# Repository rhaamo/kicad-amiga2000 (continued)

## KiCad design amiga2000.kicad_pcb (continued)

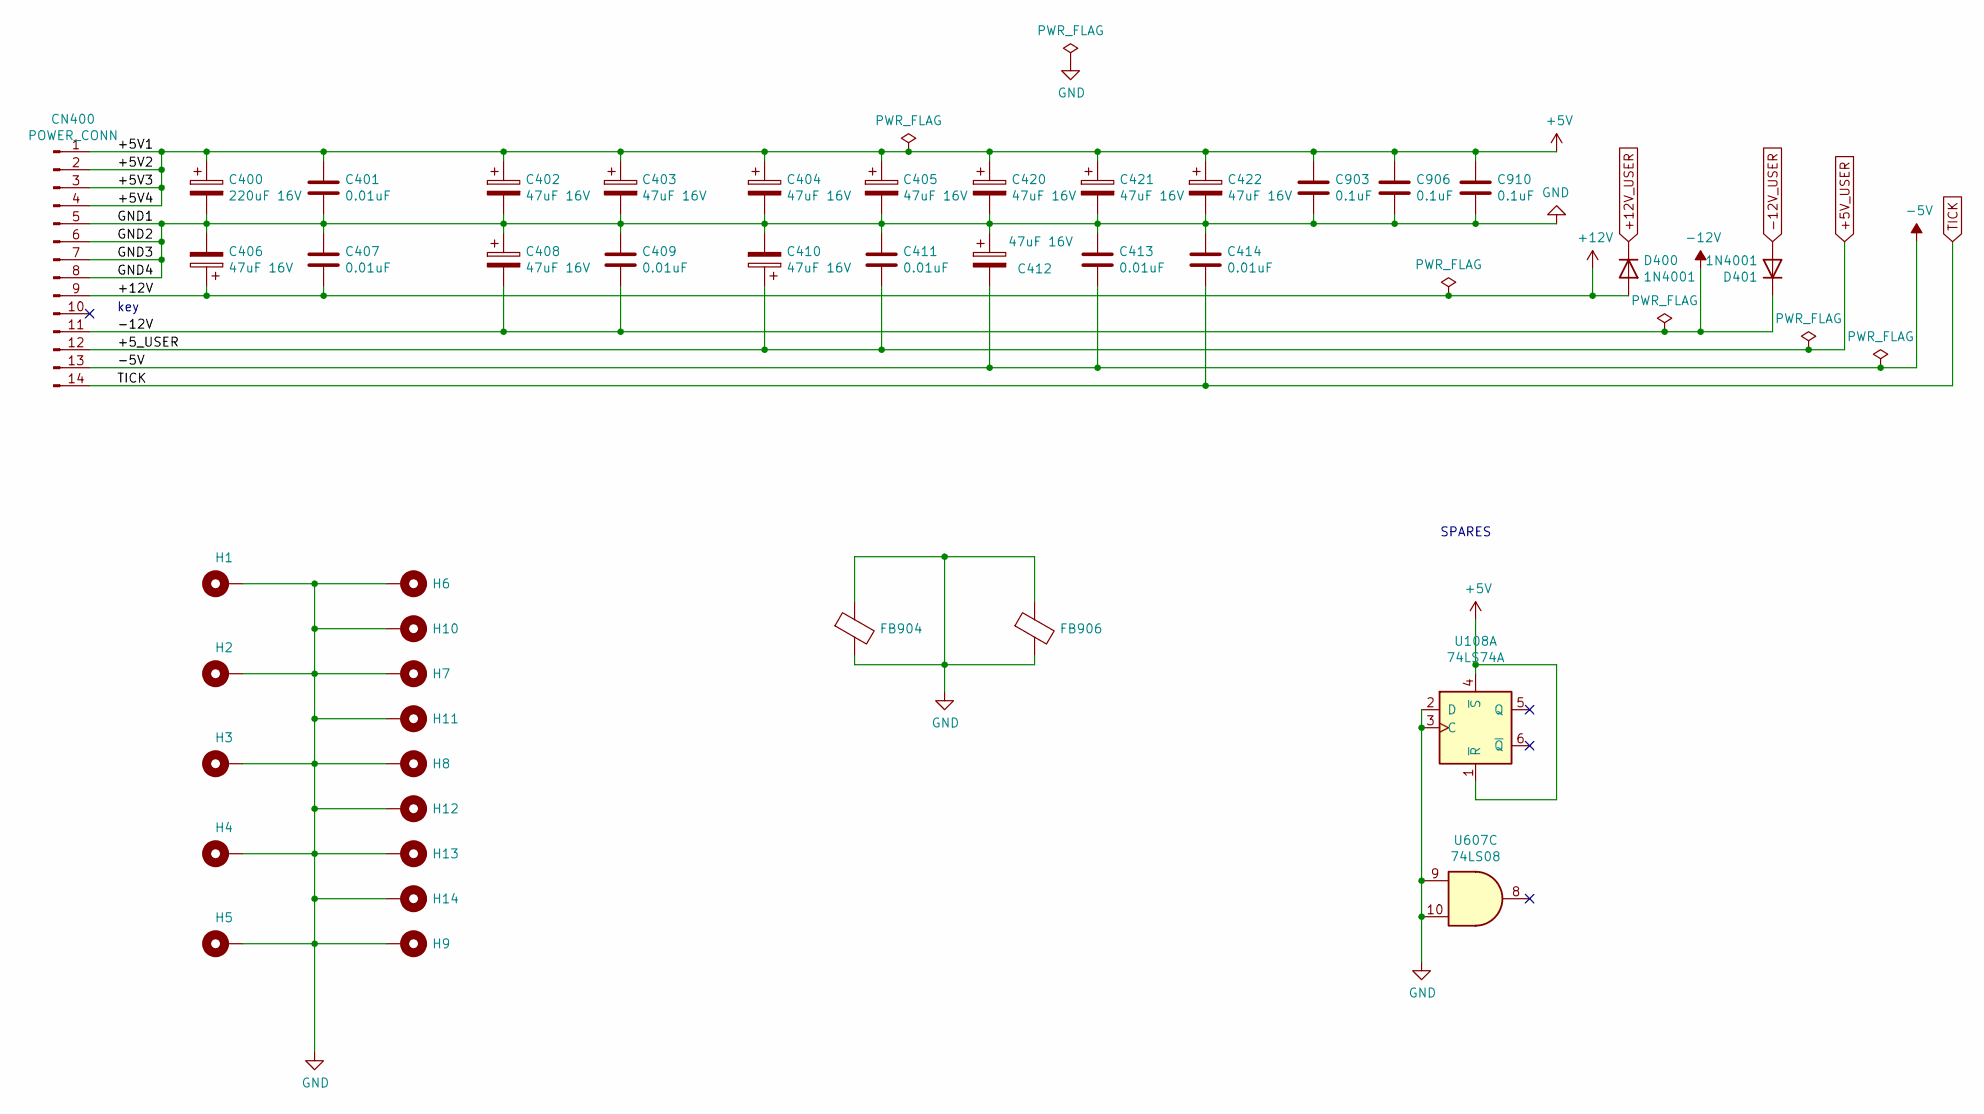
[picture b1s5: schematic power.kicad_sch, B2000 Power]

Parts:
C400: 220uF 16V; CP_Radial_Tantal_D6.0mm_P5.00mm
C401, C407, C409, C411, C413, C414: 0.01uF; C_Rect_L11.5mm_W2.6mm_P10.00mm_MKT
C402, C403, C404, C405, C406, C408, C410, C412, C420, C421, C422: 47uF 16V; CP_Radial_Tantal_D5.5mm_P5.00mm
C903, C906, C910: 0.1uF; C_Rect_L11.5mm_W2.6mm_P10.00mm_MKT
CN400: POWER_CONN; A2K_PWR
D400, D401: 1N4001; D_DO-41_SOD81_P10.16mm_Horizontal
FB904, FB906: Ferrite_Bead; L_Axial_L7.0mm_D3.3mm_P5.08mm_Vertical_Fastron_MICC
H1, H2, H3, H4, H5, H6, H7, H8, H9, H10, H11, H12, H13, H14: MountingHole_Pad; MountingHole_4mm_Pad_Via
U108: 74LS74A; DIP-14_W7.62mm_Socket
U607: 74LS08; DIP-14_W7.62mm_Socket

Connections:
+5V_USER: C410.1, C411.2, CN400.12; also elsewhere on the board
+12V: C406.1, C407.2, CN400.9, D400.2 (A); also elsewhere on the board
+12V_USER: D400.1 (K); also elsewhere on the board
-5V: C412.2, C413.2, CN400.13; also elsewhere on the board
-12V: C408.2, C409.2, CN400.11, D401.1 (K); also elsewhere on the board
-12V_USER: D401.2 (A); also elsewhere on the board
GND: C400.2, C401.2, C402.2, C403.2, C404.2, C405.2, C406.2, C407.1, C408.1, C409.1, C410.2, C411.1, C412.1, C413.1, C414.1, C420.2, C421.2, C422.2, C903.2, C906.2, C910.2, CN400.5, CN400.6, CN400.7, CN400.8, FB904.1, FB904.2, FB906.1, FB906.2, H1.1, H2.1, H3.1, H4.1, H5.1, H6.1, H7.1, H8.1, H9.1, H10.1, H11.1, H12.1, H13.1, H14.1, U108.2 (D), U108.3 (C), U607.9, U607.10; also elsewhere on the board
TICK: C414.2, CN400.14; also elsewhere on the board

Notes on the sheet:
key
SPARES

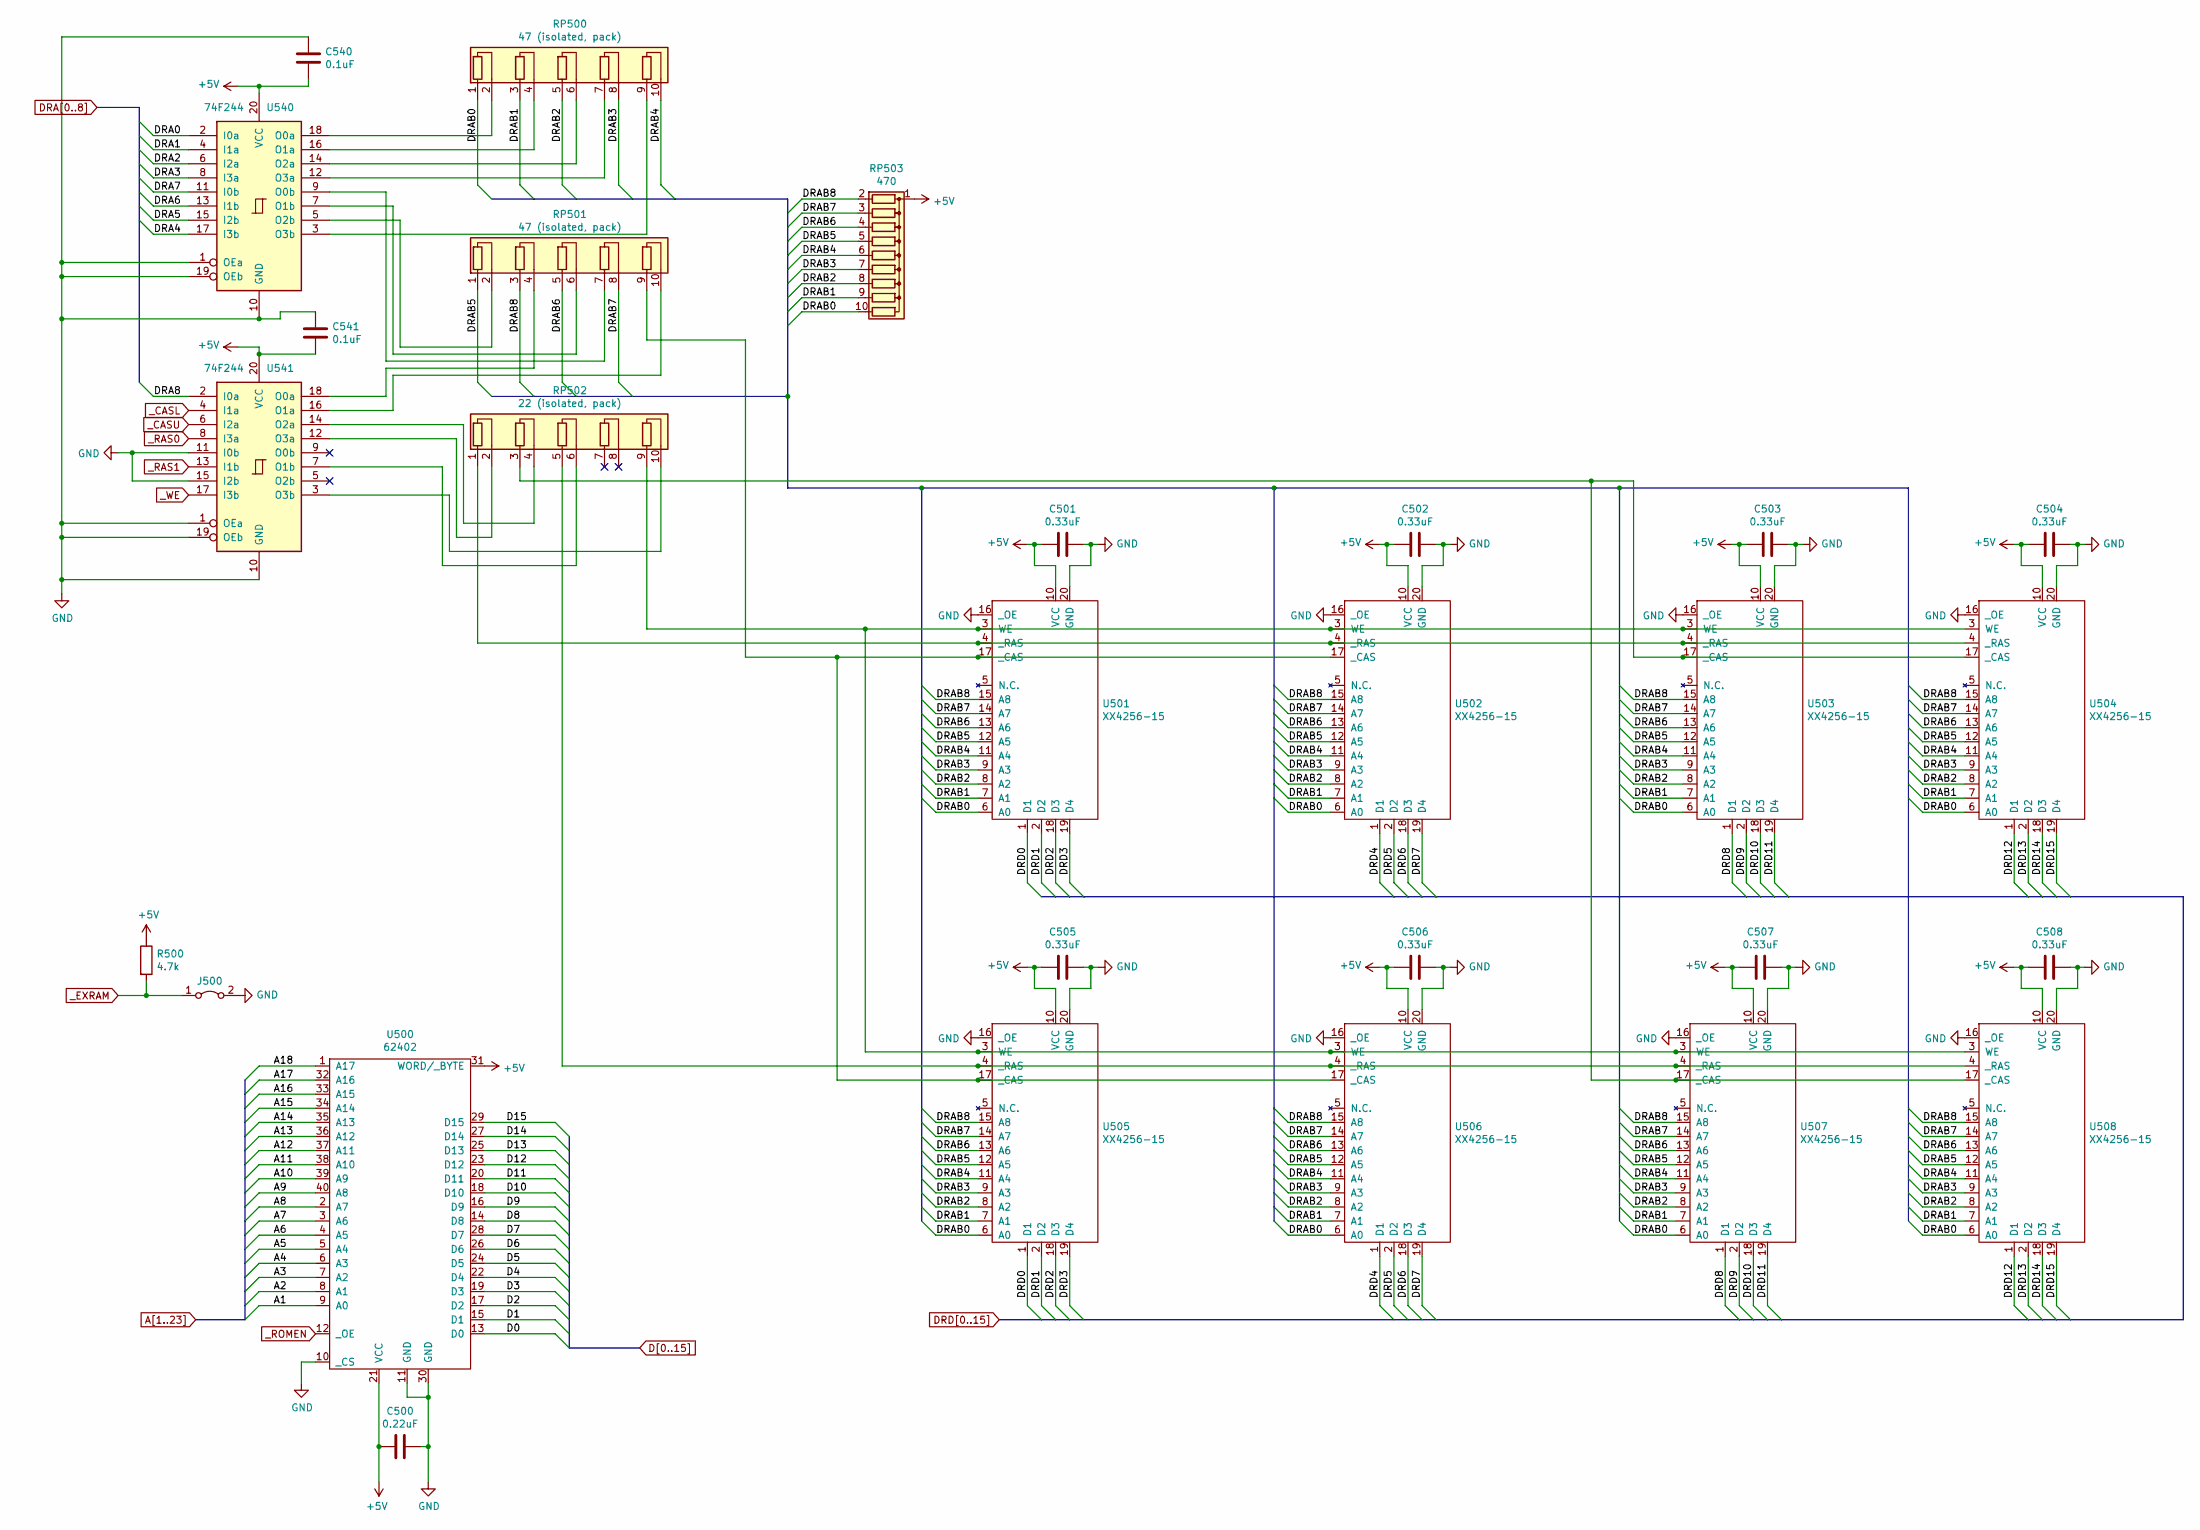
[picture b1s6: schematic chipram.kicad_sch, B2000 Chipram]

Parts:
C500: 0.22uF; C_Rect_L11.5mm_W2.6mm_P10.00mm_MKT
C501, C502, C503, C504, C505, C506, C507, C508: 0.33uF; C_Rect_L11.5mm_W4.0mm_P10.00mm_MKT
C540, C541: 0.1uF; C_Rect_L11.5mm_W2.6mm_P10.00mm_MKT
J500: Jumper_2_Bridged; PinHeader_2x01_P2.54mm_Vertical
R500: 4.7k; R_Axial_DIN0207_L6.3mm_D2.5mm_P10.16mm_Horizontal
RP500, RP501: 47 (isolated, pack); R_Array_SIP10
RP502: 22 (isolated, pack); R_Array_SIP10
RP503: 470; R_Array_SIP10
U500: 62402; DIP-40_W15.24mm_Socket
U501, U502, U503, U504, U505, U506, U507, U508: XX4256-15; DIP-20_W7.62mm_Socket
U540, U541: 74F244; DIP-20_W7.62mm_Socket

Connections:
/chipram/DRAB0: RP500.1 (R1.1), RP503.10 (R9), U501.6 (A0), U502.6 (A0), U503.6 (A0), U504.6 (A0), U505.6 (A0), U506.6 (A0), U507.6 (A0), U508.6 (A0)
/chipram/DRAB1: RP500.3 (R2.1), RP503.9 (R8), U501.7 (A1), U502.7 (A1), U503.7 (A1), U504.7 (A1), U505.7 (A1), U506.7 (A1), U507.7 (A1), U508.7 (A1)
/chipram/DRAB2: RP500.5 (R3.1), RP503.8 (R7), U501.8 (A2), U502.8 (A2), U503.8 (A2), U504.8 (A2), U505.8 (A2), U506.8 (A2), U507.8 (A2), U508.8 (A2)
/chipram/DRAB3: RP500.8 (R4.2), RP503.7 (R6), U501.9 (A3), U502.9 (A3), U503.9 (A3), U504.9 (A3), U505.9 (A3), U506.9 (A3), U507.9 (A3), U508.9 (A3)
/chipram/DRAB4: RP500.10 (R5.2), RP503.6 (R5), U501.11 (A4), U502.11 (A4), U503.11 (A4), U504.11 (A4), U505.11 (A4), U506.11 (A4), U507.11 (A4), U508.11 (A4)
/chipram/DRAB5: RP501.1 (R1.1), RP503.5 (R4), U501.12 (A5), U502.12 (A5), U503.12 (A5), U504.12 (A5), U505.12 (A5), U506.12 (A5), U507.12 (A5), U508.12 (A5)
/chipram/DRAB6: RP501.5 (R3.1), RP503.4 (R3), U501.13 (A6), U502.13 (A6), U503.13 (A6), U504.13 (A6), U505.13 (A6), U506.13 (A6), U507.13 (A6), U508.13 (A6)
/chipram/DRAB7: RP501.8 (R4.2), RP503.3 (R2), U501.14 (A7), U502.14 (A7), U503.14 (A7), U504.14 (A7), U505.14 (A7), U506.14 (A7), U507.14 (A7), U508.14 (A7)
/chipram/DRAB8: RP501.3 (R2.1), RP503.2 (R1), U501.15 (A8), U502.15 (A8), U503.15 (A8), U504.15 (A8), U505.15 (A8), U506.15 (A8), U507.15 (A8), U508.15 (A8)
A1: U500.9 (A0); also elsewhere on the board
A2: U500.8 (A1); also elsewhere on the board
A3: U500.7 (A2); also elsewhere on the board
A4: U500.6 (A3); also elsewhere on the board
A5: U500.5 (A4); also elsewhere on the board
A6: U500.4 (A5); also elsewhere on the board
A7: U500.3 (A6); also elsewhere on the board
A8: U500.2 (A7); also elsewhere on the board
A9: U500.40 (A8); also elsewhere on the board
A10: U500.39 (A9); also elsewhere on the board
A11: U500.38 (A10); also elsewhere on the board
A12: U500.37 (A11); also elsewhere on the board
A13: U500.36 (A12); also elsewhere on the board
A14: U500.35 (A13); also elsewhere on the board
A15: U500.34 (A14); also elsewhere on the board
A16: U500.33 (A15); also elsewhere on the board
A17: U500.32 (A16); also elsewhere on the board
A18: U500.1 (A17); also elsewhere on the board
D0: U500.13 (D0); also elsewhere on the board
D1: U500.15 (D1); also elsewhere on the board
D2: U500.17 (D2); also elsewhere on the board
D3: U500.19 (D3); also elsewhere on the board
D4: U500.22 (D4); also elsewhere on the board
D5: U500.24 (D5); also elsewhere on the board
D6: U500.26 (D6); also elsewhere on the board
D7: U500.28 (D7); also elsewhere on the board
D8: U500.14 (D8); also elsewhere on the board
D9: U500.16 (D9); also elsewhere on the board
D10: U500.18 (D10); also elsewhere on the board
D11: U500.20 (D11); also elsewhere on the board
D12: U500.23 (D12); also elsewhere on the board
D13: U500.25 (D13); also elsewhere on the board
D14: U500.27 (D14); also elsewhere on the board
D15: U500.29 (D15); also elsewhere on the board
DRA0: U540.2 (I0a); also elsewhere on the board
DRA1: U540.4 (I1a); also elsewhere on the board
DRA2: U540.6 (I2a); also elsewhere on the board
DRA3: U540.8 (I3a); also elsewhere on the board
DRA4: U540.17 (I3b); also elsewhere on the board
DRA5: U540.15 (I2b); also elsewhere on the board
DRA6: U540.13 (I1b); also elsewhere on the board
DRA7: U540.11 (I0b); also elsewhere on the board
DRA8: U541.2 (I0a); also elsewhere on the board
DRD0: U501.1 (D1), U505.1 (D1); also elsewhere on the board
DRD1: U501.2 (D2), U505.2 (D2); also elsewhere on the board
DRD2: U501.18 (D3), U505.18 (D3); also elsewhere on the board
DRD3: U501.19 (D4), U505.19 (D4); also elsewhere on the board
DRD4: U502.1 (D1), U506.1 (D1); also elsewhere on the board
DRD5: U502.2 (D2), U506.2 (D2); also elsewhere on the board
DRD6: U502.18 (D3), U506.18 (D3); also elsewhere on the board
DRD7: U502.19 (D4), U506.19 (D4); also elsewhere on the board
DRD8: U503.1 (D1), U507.1 (D1); also elsewhere on the board
DRD9: U503.2 (D2), U507.2 (D2); also elsewhere on the board
DRD10: U503.18 (D3), U507.18 (D3); also elsewhere on the board
DRD11: U503.19 (D4), U507.19 (D4); also elsewhere on the board
DRD12: U504.1 (D1), U508.1 (D1); also elsewhere on the board
DRD13: U504.2 (D2), U508.2 (D2); also elsewhere on the board
DRD14: U504.18 (D3), U508.18 (D3); also elsewhere on the board
DRD15: U504.19 (D4), U508.19 (D4); also elsewhere on the board
GND: C500.1, C501.1, C502.1, C503.1, C504.1, C505.1, C506.1, C507.1, C508.1, C540.1, C541.1, J500.2 (B), U500.10 (_CS), U500.11 (GND), U500.30 (GND), U501.16 (_OE), U501.20 (GND), U502.16 (_OE), U502.20 (GND), U503.16 (_OE), U503.20 (GND), U504.16 (_OE), U504.20 (GND), U505.16 (_OE), U505.20 (GND), U506.16 (_OE), U506.20 (GND), U507.16 (_OE), U507.20 (GND), U508.16 (_OE), U508.20 (GND), U540.1 (OEa), U540.10 (GND), U540.19 (OEb), U541.1 (OEa), U541.10 (GND), U541.11 (I0b), U541.15 (I2b), U541.19 (OEb); also elsewhere on the board
unnamed: RP500.2 (R1.2), U540.18 (O0a)
unnamed: RP500.4 (R2.2), U540.16 (O1a)
unnamed: RP500.6 (R3.2), U540.14 (O2a)
unnamed: RP500.7 (R4.1), U540.12 (O3a)
unnamed: RP500.9 (R5.1), U540.3 (O3b)
unnamed: RP501.2 (R1.2), U540.5 (O2b)
unnamed: RP501.4 (R2.2), U541.18 (O0a)
unnamed: RP501.6 (R3.2), U540.7 (O1b)
unnamed: RP501.7 (R4.1), U540.9 (O0b)
unnamed: RP501.9 (R5.1), U501.17 (_CAS), U502.17 (_CAS), U505.17 (_CAS), U506.17 (_CAS)
unnamed: RP501.10 (R5.2), U541.16 (O1a)
unnamed: RP502.1 (R1.1), U501.4 (_RAS), U502.4 (_RAS), U503.4 (_RAS), U504.4 (_RAS)
unnamed: RP502.2 (R1.2), U541.12 (O3a)
unnamed: RP502.3 (R2.1), U503.17 (_CAS), U504.17 (_CAS), U507.17 (_CAS), U508.17 (_CAS)
unnamed: RP502.4 (R2.2), U541.14 (O2a)
unnamed: RP502.5 (R3.1), U505.4 (_RAS), U506.4 (_RAS), U507.4 (_RAS), U508.4 (_RAS)
unnamed: RP502.6 (R3.2), U541.7 (O1b)
unnamed: RP502.9 (R5.1), U501.3 (WE), U502.3 (WE), U503.3 (WE), U504.3 (WE), U505.3 (WE), U506.3 (WE), U507.3 (WE), U508.3 (WE)
unnamed: RP502.10 (R5.2), U541.3 (O3b)
_CASL: U541.4 (I1a); also elsewhere on the board
_CASU: U541.6 (I2a); also elsewhere on the board
_EXRAM: J500.1 (A), R500.2; also elsewhere on the board
_RAS0: U541.8 (I3a); also elsewhere on the board
_RAS1: U541.13 (I1b); also elsewhere on the board
_ROMEN: U500.12 (_OE); also elsewhere on the board
_WE: U541.17 (I3b); also elsewhere on the board
